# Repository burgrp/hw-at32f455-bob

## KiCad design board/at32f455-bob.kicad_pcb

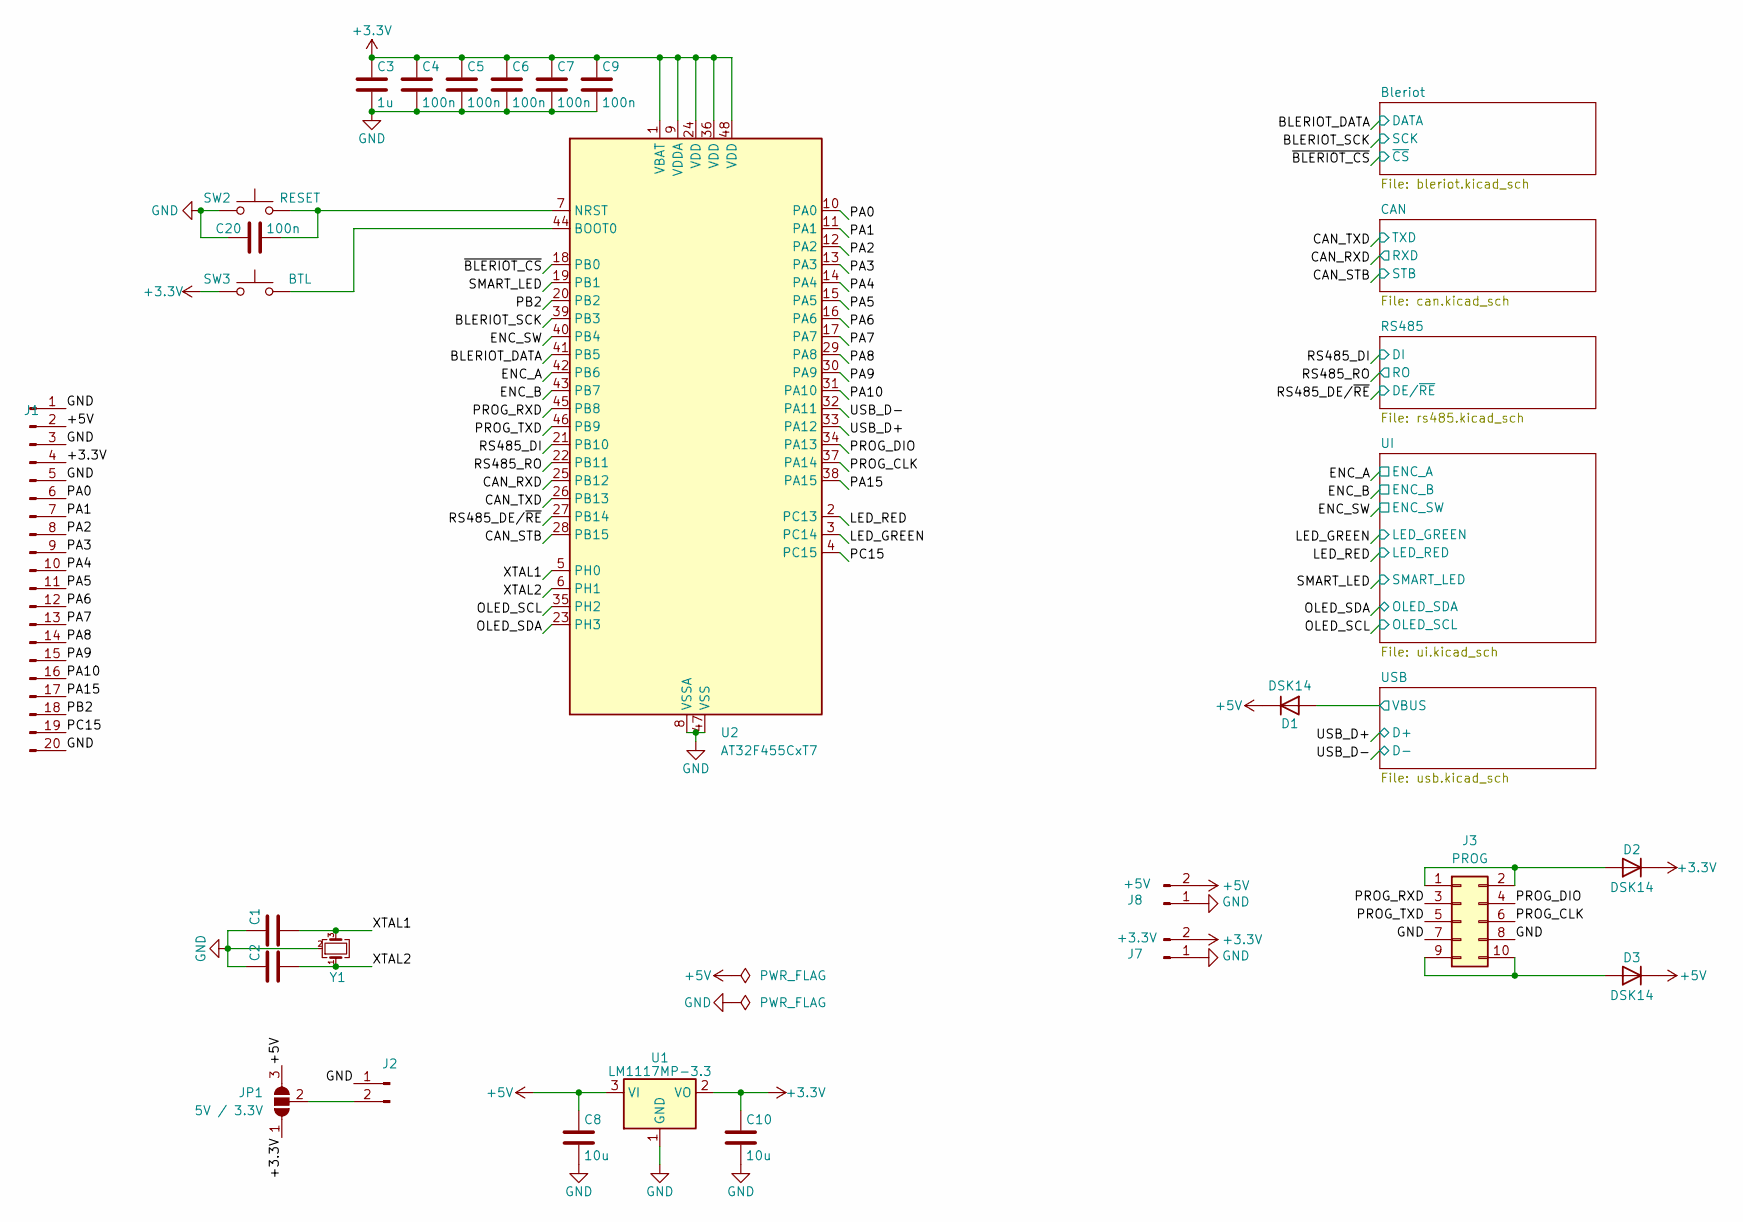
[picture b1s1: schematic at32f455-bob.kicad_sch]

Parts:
C1, C2: (mcu xtal load); C_0805_2012Metric
C3: 1u; C_0805_2012Metric
C4, C5, C6, C7, C9, C20: 100n; C_0805_2012Metric
C8, C10: 10u; C_0805_2012Metric
D1, D2, D3: DSK14; D_SOD-123
J1: BB; PinHeader_1x26_P2.54mm_Vertical
J2: PWR; PinHeader_1x02_P2.54mm_Vertical
J3: PROG; PinHeader_2x05_P2.54mm_Vertical
J7: +3.3V; PhoenixContact_MC_1,5_2-G-3.5_1x02_P3.50mm_Horizontal
J8: +5V; PhoenixContact_MC_1,5_2-G-3.5_1x02_P3.50mm_Horizontal
JP1: 5V / 3.3V; SolderJumper-3_P2.0mm_Open_TrianglePad1.0x1.5mm
SW2: RESET; SW_PUSH_6mm
SW3: BTL; SW_PUSH_6mm
U1: LM1117MP-3.3; SOT-223-3_TabPin2
U2: AT32F455CxT7; LQFP-48_7x7mm_P0.5mm
Y1: not populated; Crystal_SMD_3225-4Pin_3.2x2.5mm

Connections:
+3.3V: C3.1, C4.1, C5.1, C6.1, C7.1, C9.1, C10.1, D2.1 (K), J1.4, J7.2, JP1.1 (A), SW3.1, U1.2 (VO), U2.1 (VBAT), U2.9 (VDDA), U2.24 (VDD), U2.36 (VDD), U2.48 (VDD); also elsewhere on the board
+5V: C8.1, D1.1 (K), D3.1 (K), J1.2, J8.2, JP1.3 (B), U1.3 (VI); also elsewhere on the board
/BLERIOT_DATA: U2.41 (PB5); also elsewhere on the board
/BLERIOT_SCK: U2.39 (PB3); also elsewhere on the board
/CAN_RXD: U2.25 (PB12); also elsewhere on the board
/CAN_STB: U2.28 (PB15); also elsewhere on the board
/CAN_TXD: U2.26 (PB13); also elsewhere on the board
/ENC_A: U2.42 (PB6); also elsewhere on the board
/ENC_B: U2.43 (PB7); also elsewhere on the board
/ENC_SW: U2.40 (PB4); also elsewhere on the board
/LED_GREEN: U2.3 (PC14); also elsewhere on the board
/LED_RED: U2.2 (PC13); also elsewhere on the board
/OLED_SCL: U2.35 (PH2); also elsewhere on the board
/OLED_SDA: U2.23 (PH3); also elsewhere on the board
/PA0: J1.6, U2.10 (PA0)
/PA1: J1.7, U2.11 (PA1)
/PA2: J1.8, U2.12 (PA2)
/PA3: J1.9, U2.13 (PA3)
/PA4: J1.10, U2.14 (PA4)
/PA5: J1.11, U2.15 (PA5)
/PA6: J1.12, U2.16 (PA6)
/PA7: J1.13, U2.17 (PA7)
/PA8: J1.14, U2.29 (PA8)
/PA9: J1.15, U2.30 (PA9)
/PA10: J1.16, U2.31 (PA10)
/PA15: J1.17, U2.38 (PA15)
/PB2: J1.18, U2.20 (PB2)
/PC15: J1.19, U2.4 (PC15)
/PROG_CLK: J3.6, U2.37 (PA14)
/PROG_DIO: J3.4, U2.34 (PA13)
/PROG_RXD: J3.3, U2.45 (PB8)
/PROG_TXD: J3.5, U2.46 (PB9)
/RS485_DE/~RE: U2.27 (PB14); also elsewhere on the board
/RS485_DI: U2.21 (PB10); also elsewhere on the board
/RS485_RO: U2.22 (PB11); also elsewhere on the board
/SMART_LED: U2.19 (PB1); also elsewhere on the board
/USB/VBUS: D1.2 (A); also elsewhere on the board
/USB_D+: U2.33 (PA12); also elsewhere on the board
/USB_D-: U2.32 (PA11); also elsewhere on the board
/XTAL1: C1.2, U2.5 (PH0), Y1.3
/XTAL2: C2.2, U2.6 (PH1), Y1.1
/~BLERIOT_CS: U2.18 (PB0); also elsewhere on the board
GND: C1.1, C2.1, C3.2, C4.2, C5.2, C6.2, C7.2, C8.2, C9.2, C10.2, C20.1, J1.1, J1.3, J1.5, J1.20, J2.1, J3.7, J3.8, J7.1, J8.1, SW2.1, U1.1 (GND), U2.8 (VSSA), U2.47 (VSS), Y1.2 (G), Y1.4 (G); also elsewhere on the board
unnamed: D2.2 (A), J3.1, J3.2
unnamed: D3.2 (A), J3.9, J3.10
unnamed: J2.2, JP1.2 (C)
unnamed: SW3.2, U2.44 (BOOT0)
unnamed: C20.2, SW2.2, U2.7 (NRST)

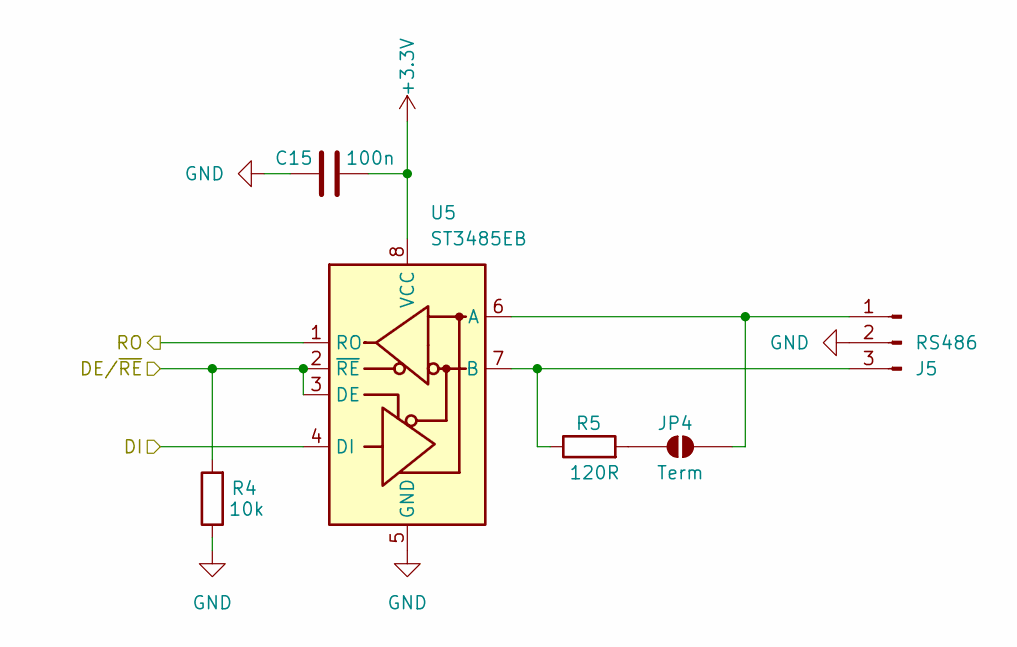
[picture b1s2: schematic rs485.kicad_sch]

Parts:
C15: 100n; C_0805_2012Metric
J5: RS486; PhoenixContact_MC_1,5_3-G-3.5_1x03_P3.50mm_Horizontal
JP4: Term; SolderJumper-2_P1.3mm_Open_TrianglePad1.0x1.5mm
R4: 10k; R_0805_2012Metric
R5: 120R; R_0805_2012Metric
U5: ST3485EB; SOIC-8_3.9x4.9mm_P1.27mm

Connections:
+3.3V: C15.2, U5.8 (VCC); also elsewhere on the board
/RS485_DE/~RE: R4.2, U5.2 (~RE), U5.3 (DE); also elsewhere on the board
/RS485_DI: U5.4 (DI); also elsewhere on the board
/RS485_RO: U5.1 (RO); also elsewhere on the board
GND: C15.1, J5.2, R4.1, U5.5 (GND); also elsewhere on the board
unnamed: J5.1, JP4.2 (B), U5.6 (A)
unnamed: J5.3, R5.1, U5.7 (B)
unnamed: JP4.1 (A), R5.2

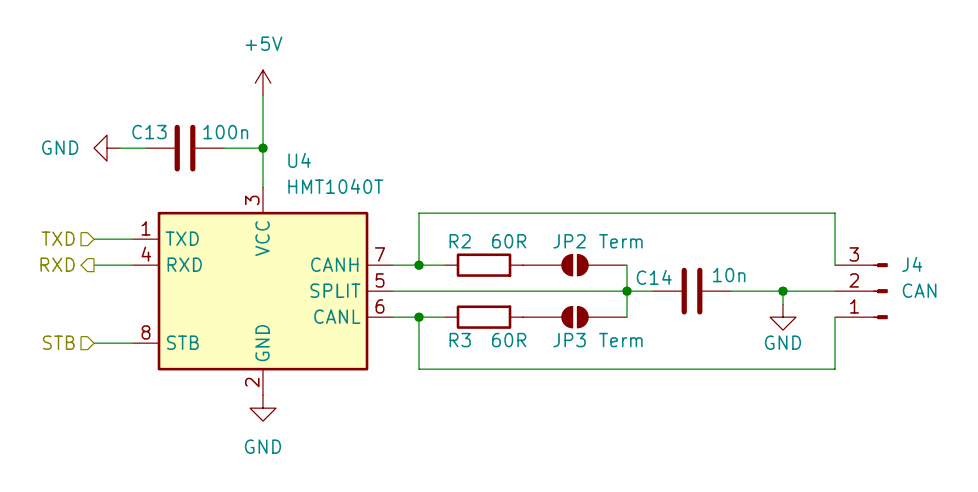
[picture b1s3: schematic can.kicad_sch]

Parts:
C13: 100n; C_0805_2012Metric
C14: 10n; C_0805_2012Metric
J4: CAN; PhoenixContact_MC_1,5_3-G-3.5_1x03_P3.50mm_Horizontal
JP2, JP3: Term; SolderJumper-2_P1.3mm_Open_TrianglePad1.0x1.5mm
R2, R3: 60R; R_0805_2012Metric
U4: HMT1040T; SOIC-8_3.9x4.9mm_P1.27mm

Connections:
+5V: C13.2, U4.3 (VCC); also elsewhere on the board
/CAN_RXD: U4.4 (RXD); also elsewhere on the board
/CAN_STB: U4.8 (STB); also elsewhere on the board
/CAN_TXD: U4.1 (TXD); also elsewhere on the board
GND: C13.1, C14.2, J4.2, U4.2 (GND); also elsewhere on the board
unnamed: J4.1, R3.1, U4.6 (CANL)
unnamed: J4.3, R2.1, U4.7 (CANH)
unnamed: JP2.1 (A), R2.2
unnamed: C14.1, JP2.2 (B), JP3.2 (B), U4.5 (SPLIT)
unnamed: JP3.1 (A), R3.2

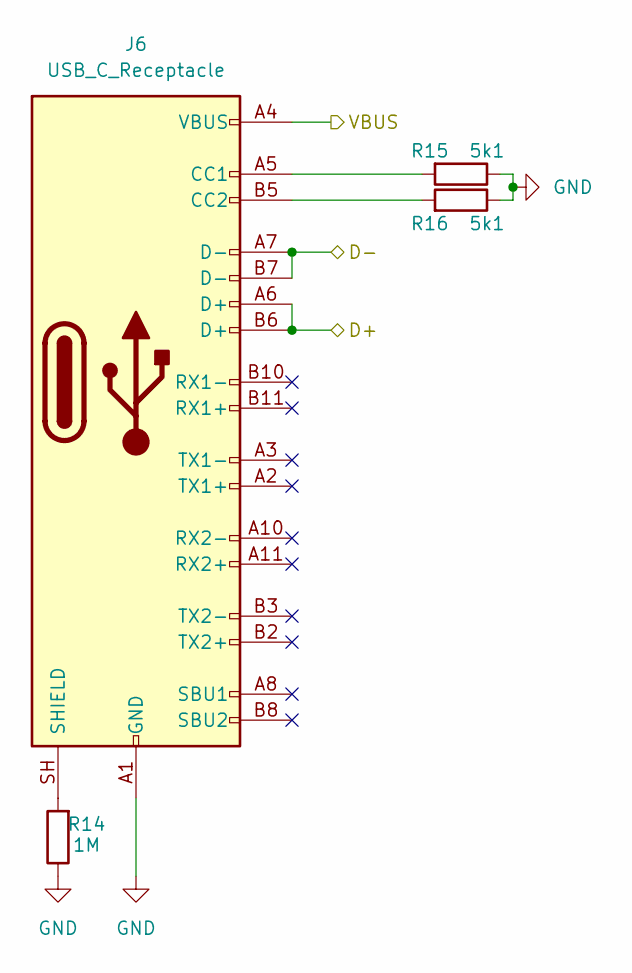
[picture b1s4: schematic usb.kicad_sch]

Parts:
J6: USB_C_Receptacle; USB_C_Receptacle-Handsolder
R14: 1M; R_0805_2012Metric
R15, R16: 5k1; R_0805_2012Metric

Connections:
/USB/VBUS: J6.A4 (VBUS), J6.A9 (VBUS), J6.B4 (VBUS), J6.B9 (VBUS); also elsewhere on the board
/USB_D+: J6.A6 (D+), J6.B6 (D+); also elsewhere on the board
/USB_D-: J6.A7 (D-), J6.B7 (D-); also elsewhere on the board
GND: J6.A1 (GND), J6.A12 (GND), J6.B1 (GND), J6.B12 (GND), R14.1, R15.1, R16.1; also elsewhere on the board
unnamed: J6.A5 (CC1), R15.2
unnamed: J6.B5 (CC2), R16.2
unnamed: J6.SH (SHIELD), R14.2

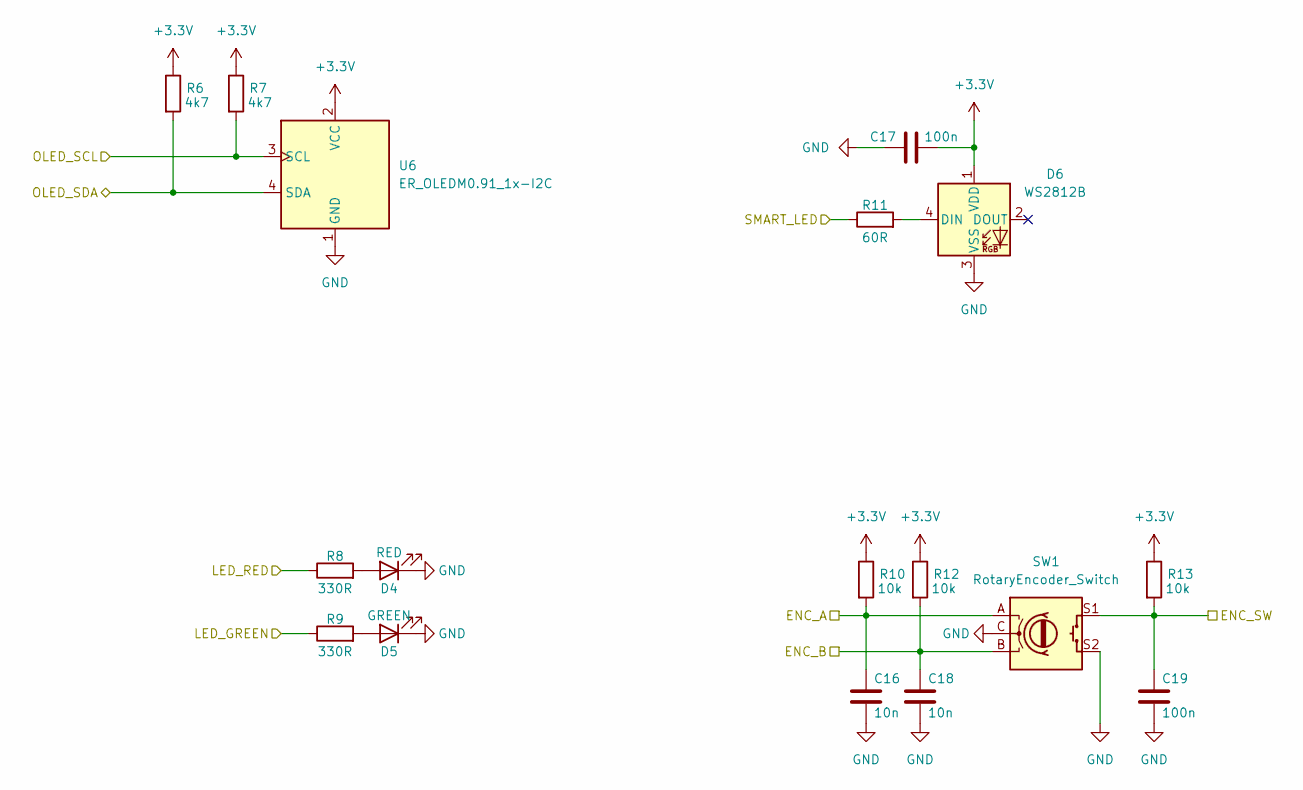
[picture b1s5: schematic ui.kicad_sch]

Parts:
C16, C18: 10n; C_0805_2012Metric
C17, C19: 100n; C_0805_2012Metric
D4: RED; LED_0805_2012Metric
D5: GREEN; LED_0805_2012Metric
D6: WS2812B; LED_WS2812B_PLCC4_5.0x5.0mm_P3.2mm
R6, R7: 4k7; R_0805_2012Metric
R8, R9: 330R; R_0805_2012Metric
R10, R12, R13: 10k; R_0805_2012Metric
R11: 60R; R_0805_2012Metric
SW1: RotaryEncoder_Switch; RotaryEncoder_Alps_EC11E-Switch_Vertical_H20mm
U6: ER_OLEDM0.91_1x-I2C

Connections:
+3.3V: C17.2, D6.1 (VDD), R6.1, R7.1, R10.1, R12.1, R13.1, U6.2 (VCC); also elsewhere on the board
/ENC_A: C16.2, R10.2, SW1.A; also elsewhere on the board
/ENC_B: C18.2, R12.2, SW1.B; also elsewhere on the board
/ENC_SW: C19.2, R13.2, SW1.S1; also elsewhere on the board
/LED_GREEN: R9.1; also elsewhere on the board
/LED_RED: R8.1; also elsewhere on the board
/OLED_SCL: R7.2, U6.3 (SCL); also elsewhere on the board
/OLED_SDA: R6.2, U6.4 (SDA); also elsewhere on the board
/SMART_LED: R11.1; also elsewhere on the board
GND: C16.1, C17.1, C18.1, C19.1, D4.1 (K), D5.1 (K), D6.3 (VSS), SW1.C, SW1.S2, U6.1 (GND); also elsewhere on the board
unnamed: D4.2 (A), R8.2
unnamed: D5.2 (A), R9.2
unnamed: D6.4 (DIN), R11.2

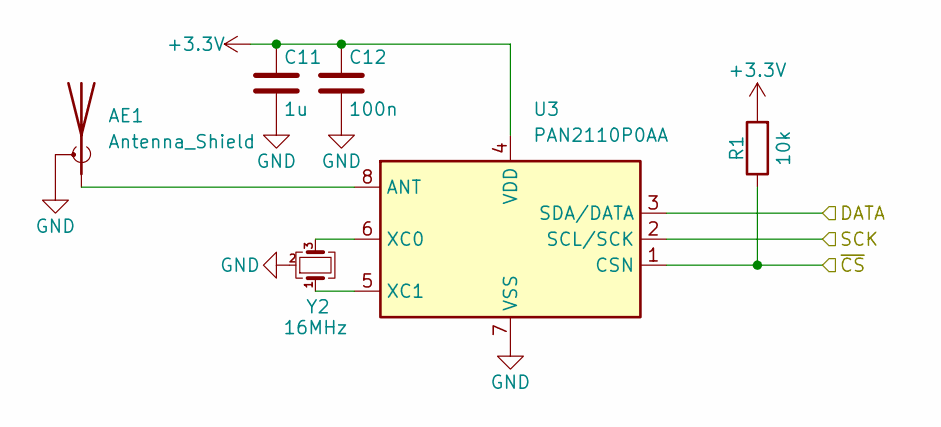
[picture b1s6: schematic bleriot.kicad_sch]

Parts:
AE1: Antenna_Shield; Texas_SWRA117D_2.4GHz_Right
C11: 1u; C_0805_2012Metric
C12: 100n; C_0805_2012Metric
R1: 10k; R_0805_2012Metric
U3: PAN2110P0AA; SOIC-8_3.9x4.9mm_P1.27mm
Y2: 16MHz; Crystal_SMD_3225-4Pin_3.2x2.5mm

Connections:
+3.3V: C11.1, C12.1, R1.2, U3.4 (VDD); also elsewhere on the board
/BLERIOT_DATA: U3.3 (SDA/DATA); also elsewhere on the board
/BLERIOT_SCK: U3.2 (SCL/SCK); also elsewhere on the board
/~BLERIOT_CS: R1.1, U3.1 (CSN); also elsewhere on the board
GND: AE1.2 (Shield), C11.2, C12.2, U3.7 (VSS), Y2.2 (G), Y2.4 (G); also elsewhere on the board
unnamed: AE1.1 (A), U3.8 (ANT)
unnamed: U3.6 (XC0), Y2.3
unnamed: U3.5 (XC1), Y2.1

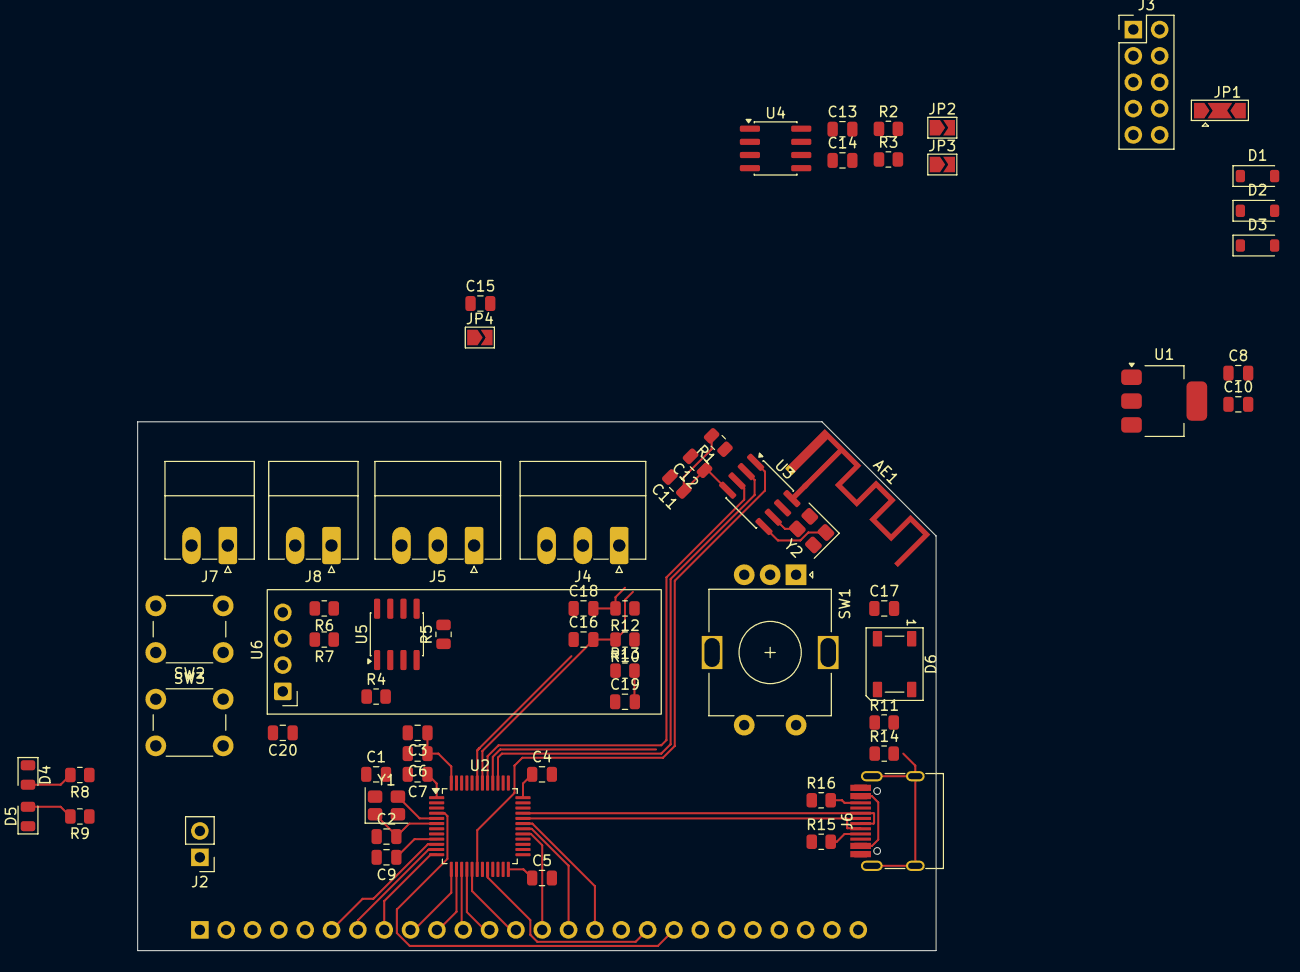
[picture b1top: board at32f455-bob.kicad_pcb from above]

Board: 2 copper layers, 77.0 x 51.0 mm, 66 parts (1 on the bottom side), 65 nets.
